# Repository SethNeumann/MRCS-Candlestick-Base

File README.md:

# MRCS-Candlestick-Base
## License: Creative Commons Attribution-NonCommercial-ShareAlike

Wiring base for MRCS-Candlestick-Mic electret carbon mic replacement

Initial version

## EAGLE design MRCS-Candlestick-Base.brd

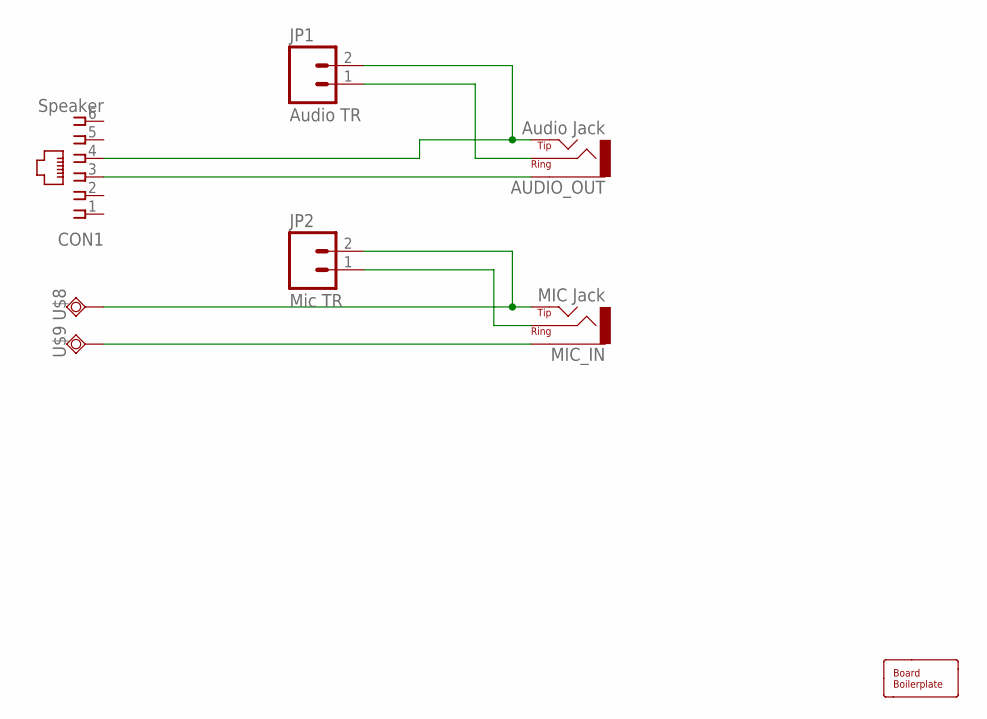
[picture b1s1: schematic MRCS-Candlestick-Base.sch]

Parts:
AUDIO_OUT: Audio Jack; AUDIO-JACK-3.5MM_STEREO
BOARD1: BOARD69X50; BOARD-DINRAIL-2.7IN-5CM
CON1: Speaker; RJ25-INVERTED
JP1: Audio TR; MOLEX-1X2_LOCK
JP2: Mic TR; MOLEX-1X2_LOCK
MIC_IN: MIC Jack; AUDIO-JACK-3.5MM_STEREO
U$8, U$9: SPADELUG.4; SPADELUGPAD

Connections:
unnamed: AUDIO_OUT.TIP, CON1.4, JP1.2 (B)
unnamed: AUDIO_OUT.GND (SLEEVE), CON1.3
unnamed: AUDIO_OUT.RING, JP1.1 (A)
unnamed: MIC_IN.GND (SLEEVE), U$9.P1
unnamed: JP2.2 (B), MIC_IN.TIP, U$8.P1
unnamed: JP2.1 (A), MIC_IN.RING

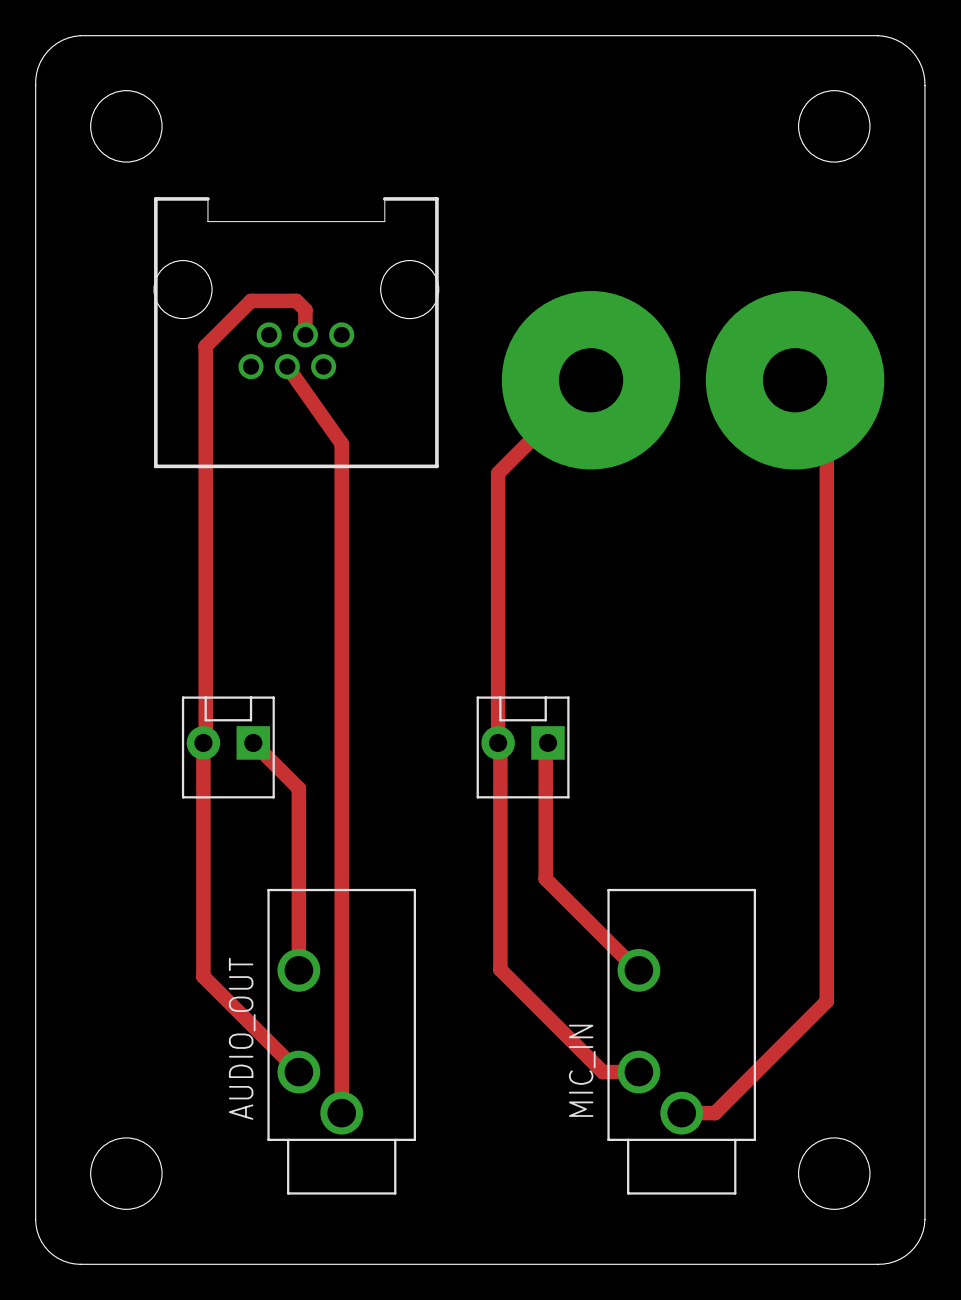
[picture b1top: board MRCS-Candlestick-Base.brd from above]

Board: 2 copper layers, 49.8 x 68.8 mm, 11 parts (0 on the bottom side), 6 nets.

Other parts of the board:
U$5: MRCSLOGOTOP
U$6: MRCSLOGOBTM
U$7: CA-PROP65-BACK

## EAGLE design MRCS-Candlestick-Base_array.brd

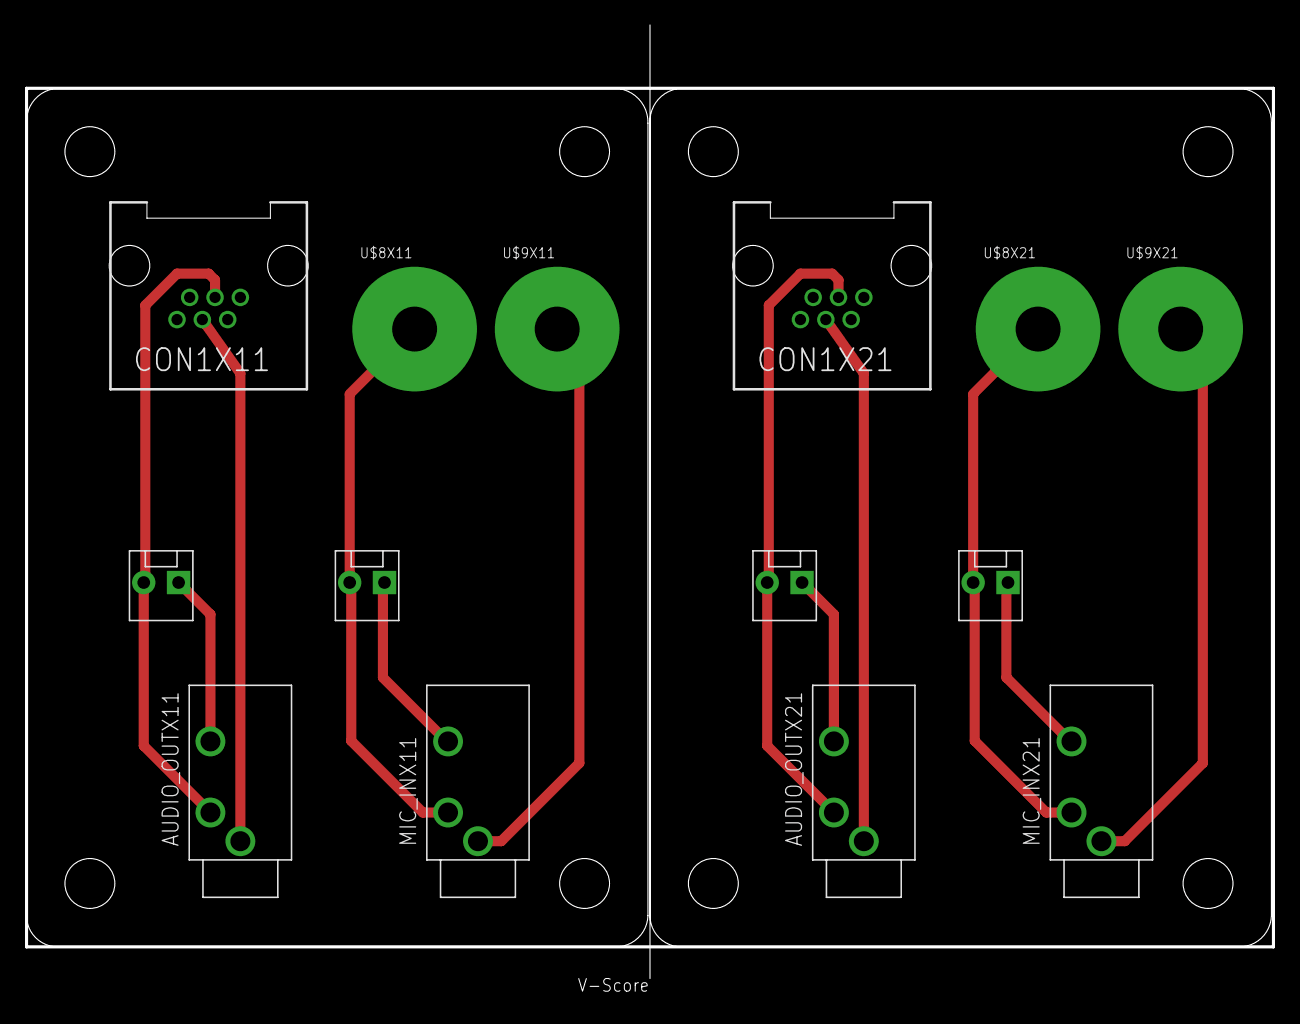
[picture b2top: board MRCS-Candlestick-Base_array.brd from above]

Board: 2 copper layers, 100.0 x 77.8 mm, 22 parts (0 on the bottom side), 12 nets.

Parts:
AUDIO_OUTX11, AUDIO_OUTX21: AUDIO-JACK-3.5MM_STEREO
BOARD1X11, BOARD1X21: BOARD-DINRAIL-2.7IN-5CM
CON1X11, CON1X21: RJ25-INVERTED
JP1X11, JP1X21, JP2X11, JP2X21: MOLEX-1X2_LOCK
MIC_INX11, MIC_INX21: AUDIO-JACK-3.5MM_STEREO
U$5X11, U$5X21: MRCSLOGOTOP
U$6X11, U$6X21: MRCSLOGOBTM
U$7X11, U$7X21: CA-PROP65-BACK
U$8X11, U$8X21, U$9X11, U$9X21: SPADELUGPAD

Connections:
unnamed: AUDIO_OUTX11.TIP, CON1X11.4, JP1X11.2
unnamed: AUDIO_OUTX21.TIP, CON1X21.4, JP1X21.2
unnamed: AUDIO_OUTX11.GND, CON1X11.3
unnamed: AUDIO_OUTX21.GND, CON1X21.3
unnamed: AUDIO_OUTX11.RING, JP1X11.1
unnamed: AUDIO_OUTX21.RING, JP1X21.1
unnamed: MIC_INX11.GND, U$9X11.P1
unnamed: MIC_INX21.GND, U$9X21.P1
unnamed: JP2X11.2, MIC_INX11.TIP, U$8X11.P1
unnamed: JP2X21.2, MIC_INX21.TIP, U$8X21.P1
unnamed: JP2X11.1, MIC_INX11.RING
unnamed: JP2X21.1, MIC_INX21.RING

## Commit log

2019-11-29 Initial version
2019-11-29 panelized
2019-12-07 added arrag script
2020-05-04 updated tags
